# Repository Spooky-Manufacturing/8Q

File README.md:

# 8Q
<!-- ALL-CONTRIBUTORS-BADGE:START - Do not remove or modify this section -->

<!-- ALL-CONTRIBUTORS-BADGE:END -->

Computer with built-in General Purpose 8 Qubit Optical Quantum Processor

# Contributors
[Thank you to all the contributors who make this possible](./CONTRIBUTORS.md)

# Status: Moving Towards PCB!

We're beginning to layout the components and finalize the design of our quantum computer! As we continue to design the PCB, we are also working with optical engineers to make our logic gates more compact which will enable us to shrink the design even further than we already have!

### Development Board

To speed up R&D, we've decided to replace the ARM CPU with a QSeven2.0 spec'd "computer on module". There are a variety of benefits to doing this, one major benefit being that we can switch between a variety of x86 and ARM processors.

The current design effort utilizes the Congatech A50 CoM.

### Quantum Processing Unit

### QController

The QController acts as a bridge between the main (digital) computer and the quantum processor. It is responsible for storing/executing instructions, and for transferring data to/from the host and QPU.

## Features

* Quad-Core Cortex-A53
* Mali-T720 MP2 GPU
* 1x DDR4 Ram Slot (Max 64GB)
* 32/64 Bit Compatible
* Linux Capable

## Files

#### Hardware Design Files

| Type                | Directory   | Filename         | Description                |
| ------------------- | ----------- | ---------------- | -------------------------- |
| Project File        | [8Q/](./8Q) | 8Q.pro           | Main KiCAD Project File    |
| PCB Design File     | [8Q/](./8Q) | 8Q.kicad_PCB     | Main KiCAD PCB File        |
| Board Schematic     | [8Q/](./8Q) | cpu.sch          | Main CPU Schematic         |
| Board Schematic     | [8Q/](./8Q) | cpu_power.sch    | CPU Power Schematic        |
| Board Schematic     | [8Q/](./8Q) | RAM.sch          | CPU RAM Schematic          |
| QCore Schematic     | [8Q/](./8Q) | qpu.sch          | Main QPU Schematic         |
| QCore Schematic     | [8Q/](./8Q) | qpower.sch       | QPU Power Schematic        |
| QCore Schematic     | [8Q/](./8Q) | preprocessor.sch | QPU Control Unit Schematic |
| Manufacturing Files | 8Q/gerber   | none             | none (gerber files)        |
| Manufacturing Files | 8Q/assembly | none             | none (assembly files)      |

#### Documentation Files

| Type              | Directory                     | Filename         | Description                                |
| ----------------- | ----------------------------- | ---------------- | ------------------------------------------ |
| Makefile          | [docs/](./docs)               | Makefile         | Used to build documentation                |
| Folder            | [docs/build/](./docs/build)   | *                | Build files for docs                       |
| Folder            | [docs/source/](./docs/source) | *                | Documentation source files                 |
| Folder            | [docs/source/imgs/](./docs/source/imgs) | *      | Image files                                |
| ReStructured Text | [docs/source/](./docs/source) | architecture.rst | Instruction Set Architecture Documentation |
| ReStructured Text | [docs/source/](./docs/source) | board.rst        | Board Hardware Information                 |
| Python            | [docs/source/](./docs/source) | conf.py          | Docs Generator Configs                     |
| ReStructured Text | [docs/source/](./docs/source) | index.rst        | Documentation Home Page                    |
| ReStructured Text | [docs/source/](./docs/source) | programming.rst  | Programming Documentation                  |

#### Firmware/Software Sources

None: [src/](./src)

#### Development Tools

None: [tools/](./tools)

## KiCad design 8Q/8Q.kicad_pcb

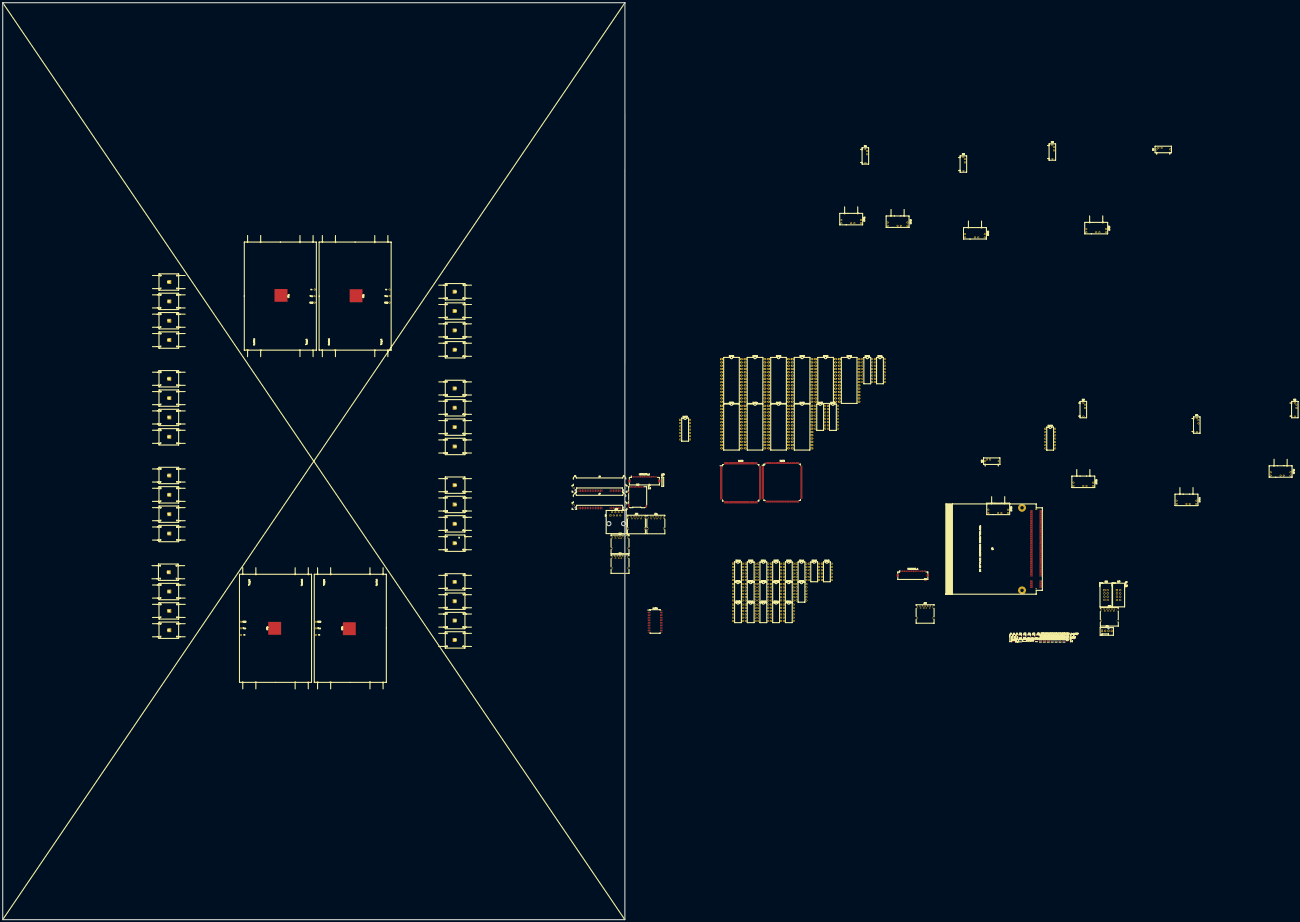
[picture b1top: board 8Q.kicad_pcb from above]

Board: 2 copper layers, 482.5 x 711.0 mm, 157 parts (0 on the bottom side), 266 nets, no tracks yet.

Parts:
C262292_1, C262292_2: LVDS Display; Hirose_FH12-40S-0.5SH_1x40-1MP_P0.50mm_Horizontal
CH1: Macro-CH-Gate; CH-Gate
CX1: Macro-CX-Gate; CX-Gate
CY1: Macro-CY-Gate; CY-Gate
CZ1: Macro-CZ-Gate; CZ-Gate
D1: GreenLED; LED_0603_1608Metric
D2: BlueLED; LED_0603_1608Metric
D5, D6, D7, D8, D9, D10, D11, D12, D13, D14, D15, D16, D17, D18, D19, D20: 1SS367,H3F; D_SOD-323
H1, H2, H3, H4, H5, H6, H7, H8: Macro-H-Gate; H-Gate
J1: TEMP; PinHeader_1x02_P1.00mm_Vertical
J2: 1 WIRE BUS; PinHeader_1x01_P1.00mm_Vertical
J3: SMBUS; PinHeader_1x03_P1.00mm_Vertical
J4: GP0_I2C; PinHeader_1x02_P1.00mm_Vertical
J5: HDA/I2C; PinHeader_1x05_P1.00mm_Vertical
J6: SATA0; SATA_Amphenol_10029364-001LF_Horizontal
J7: SATA1; SATA_Amphenol_10029364-001LF_Horizontal
J8: CAN BUS; PinHeader_1x02_P1.00mm_Vertical
J9: UART; PinHeader_1x04_P1.00mm_Vertical
J12: 8P8C_LED_Shielded; RJ45_Amphenol_54602-x08_Horizontal
J13: Watchdog; PinHeader_1x02_P1.00mm_Vertical
J15: SD_Card; microSD_HC_Hirose_DM3AT-SF-PEJM5
J19: BIOS_DISABLE; PinHeader_1x02_P1.00mm_Vertical
J20: AVR-JTAG-10; IDC-Header_2x04_P2.54mm_Vertical
J21: USB3_A; USB3_A_Molex_48393-001
J22: LDC; IDC-Header_2x04_P2.54mm_Vertical
J23: GPIO; PinHeader_1x08_P1.00mm_Vertical
J24, J25, J26, J27, J28: USB_A; USB3_A_Molex_48393-001
M1, M2, M3, M4, M5, M6, M7, M8: Macro-Measure; Measure
M9: CPU_FAN; FanPinHeader_1x04_P2.54mm_Vertical
Q1, Q2, Q3, Q4: Q_PNP_BCE; SOT-23
Q5: Q_NPN_BCE; SOT-23
Q6: Q7; MXM2.0
R1, R2, R3, R4: 10k; R_0402_1005Metric
R5, R6, R7, R8: 1k; R_0402_1005Metric
R9: 10ohm; R_0402_1005Metric
R10: 1M; R_0402_1005Metric
SPE1, SPE2, SPE3, SPE4, SPE5, SPE6, SPE7, SPE8: Macro-Photon-Source; Photon-Source
U1, U2, U180, U182, U184, U185, U186, U187: USBLC6-2P6; SOT-666
U175, U176: HEF4093B; DIP-14_W7.62mm
U178: S5933_PQ160; PQFP-160_28x28mm_P0.65mm
U179: STM32F429BITx; LQFP-208_28x28mm_P0.5mm
U181, U183, U196, U197: 74LS590; DIP-16_W7.62mm
U188, U189, U192, U193, U194, U195, U198, U199, U204, U205: 28C256; DIP-28_W15.24mm_LongPads
U208: FM1608B-SG; SOIC-28W_7.5x17.9mm_P1.27mm
U210, U211, U212, U213, U214, U215, U216, U217, U218, U219, U220, U221, U222, U223, U224, U225, U226, U227, U228: 74LS243; DIP-12_W7.62mm
X1, X2, X3, X4, X5, X6, X7, X8: Macro-X-Gate; X-Gate
Y1, Y2, Y3, Y4, Y5, Y6, Y7, Y8: Macro-Y-Gate; Y-Gate
Z1, Z2, Z3, Z4, Z5, Z6, Z7, Z8: Macro-Z-Gate; Z-Gate

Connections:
+3V3: C262292_1.2, C262292_1.3, C262292_2.2, C262292_2.3, J20.4, J20.7, Q5.2
+5V: M1.3, M2.3, M3.3, M4.3, M5.3, M6.3, M7.3, M8.3, Q6.205, Q6.206, Q6.211, Q6.212, Q6.213, Q6.214, Q6.215, Q6.216, Q6.217, Q6.218, Q6.219, Q6.220, Q6.221, Q6.222, Q6.223, Q6.224, Q6.225, Q6.226, Q6.227, Q6.228, Q6.229, Q6.230, R1.1, R2.1, R3.1, R4.1, U188.20, U188.28, U189.20, U189.28, U192.20, U192.28, U193.20, U193.28, U194.20, U194.28, U195.20, U195.28, U198.20, U198.28, U199.20, U199.28, U204.20, U204.28, U205.20, U205.28, U208.28
BIOS_DISABLE: J19.2, Q6.41
CAN0_RX: J8.2, Q6.130
CAN0_TX: J8.1, Q6.129
CCD: U210.6, U210.8
CH: U219.5, U219.9
CQ1D: U210.3, U210.11
CQ2D: U210.4, U210.10
CQ3D: U210.5, U210.9
CTD: U228.3, U228.11
CY: U219.3, U219.11
CZ: U219.4, U219.10
DP_HDMI_HPD: C262292_1.7, C262292_1.10, C262292_1.13, C262292_1.16, C262292_1.19, C262292_1.22, C262292_1.25, C262292_1.30, C262292_2.7, C262292_2.10, C262292_2.13, C262292_2.16, C262292_2.19, C262292_2.22, C262292_2.25, C262292_2.30, CH1.10, CX1.10, CY1.10, CZ1.10, D5.2, D6.2, D7.2, D8.2, D9.2, D10.2, D11.2, D12.2, D13.2, D14.2, D15.2, D16.2, D17.2, D18.2, D19.2, D20.2, J19.1, J20.2, J24.4, J24.5, J25.4, J25.5, J26.4, J26.5, J27.4, J27.5, J28.4, J28.5, M1.4, M2.4, M3.4, M4.4, M5.4, M6.4, M7.4, M8.4, M9.1, Q1.2, Q2.2, Q3.2, Q4.2, Q6.1, Q6.2, Q6.23, Q6.24, Q6.25, Q6.34, Q6.39, Q6.40, Q6.57, Q6.58, Q6.73, Q6.74, Q6.97, Q6.98, Q6.117, Q6.118, Q6.135, Q6.136, Q6.141, Q6.142, Q6.147, Q6.148, Q6.153, Q6.159, Q6.160, Q6.165, Q6.166, Q6.183, Q6.184, Q6.197, Q6.198, R9.2, R10.2, SPE1.8, SPE2.8, SPE3.8, SPE4.8, SPE5.8, SPE6.8, SPE7.8, SPE8.8, U1.2, U2.2, U180.2, U182.2, U184.2, U185.2, U186.2, U187.2, U208.14, U210.7, U211.7, U212.7, U213.7, U214.7, U215.7, U216.7, U217.7, U218.7, U219.7, U220.7, U221.7, U222.7, U223.7, U224.7, U225.7, U226.7, U227.7, U228.7
FAN_PWM: M9.4, Q6.196
FAN_TACHO: M9.3, Q6.195
GBE0+: J12.1, Q6.12
GBE0-: J12.2, Q6.10
GBE1+: J12.3, Q6.11
GBE1-: J12.6, Q6.9
GBE2+: J12.4, Q6.6
GBE2-: J12.5, Q6.4
GBE3+: J12.7, Q6.5
GBE3-: J12.8, Q6.3
GBE_10: Q6.13, R8.2
GBE_100: Q6.7, R5.2
GBE_1000: Q6.8, R6.2
GBE_ACT: Q6.14, R7.1
GNDA: SPE1.7, SPE2.7, SPE3.7, SPE4.7, SPE5.7, SPE6.7, SPE7.7, SPE8.7
GP0_I2C_CLK: J4.1, Q6.66
GP1_WIRE_BUS: J2.1, Q6.124
GPO_I2C_DAT: J4.2, Q6.68
HDA_BITCLK: J5.3, Q6.63
HDA_RST: J5.2, Q6.61
HDA_SDI: J5.4, Q6.65
HDA_SDO: J5.5, Q6.67
HDA_SYNC: J5.1, Q6.59
JTAG_TCK: J20.1, Q6.207
JTAG_TDO: J20.3, Q6.209
JTAG_TMS: J20.5, Q6.210
JTAG_TRST: J20.8, Q6.204
LPC_AD0_GPIO0: J22.3, J23.1, Q6.185
LPC_AD1_GPIO1: J22.7, J23.2, Q6.186
LPC_AD2_GPIO2: J22.4, J23.3, Q6.187
LPC_AD3_GPIO3: J22.8, J23.4, Q6.188
LPC_CLK_GPIO4: J22.1, J23.5, Q6.189
LPC_FRAME_GPIO5: J22.5, J23.6, Q6.190
LPC_LDRQ_GPIO7: J22.6, J23.8, Q6.192
LVDS_A0+: C262292_1.9, Q6.99
LVDS_A0-: C262292_1.8, Q6.101
LVDS_A1+: C262292_1.12, Q6.103
LVDS_A1-: C262292_1.11, Q6.105
LVDS_A2+: C262292_1.15, Q6.107
LVDS_A2-: C262292_1.14, Q6.109
LVDS_A3+: C262292_1.21, Q6.113
LVDS_A3-: C262292_1.20, Q6.115
LVDS_A_CLK+: C262292_1.18, Q6.119
LVDS_A_CLK-: C262292_1.17, Q6.121
LVDS_B0+: C262292_2.9, Q6.100
LVDS_B0-: C262292_2.8, Q6.102
LVDS_B1+: C262292_2.12, Q6.104
LVDS_B1-: C262292_2.11, Q6.106
LVDS_B2+: C262292_2.15, Q6.108
LVDS_B2-: C262292_2.14, Q6.110
LVDS_B3+: C262292_2.21, Q6.114
LVDS_B3-: C262292_2.20, Q6.116
LVDS_BLT_CTRL: C262292_1.27, C262292_2.27, Q6.123
LVDS_B_CLK+: C262292_2.18, Q6.120
LVDS_B_CLK-: C262292_2.17, Q6.122
LVDS_DID_CLK: C262292_1.24, C262292_2.24, Q6.127
LVDS_DID_DAT: C262292_1.23, C262292_2.23, Q6.125
LVDS_PPEN: C262292_1.26, C262292_2.26, Q6.111
unnamed: D1.1, Q1.3
unnamed: D1.2, R1.2
unnamed: D2.1, Q4.3
unnamed: D2.2, R2.2
unnamed: J15.3, J15.6
unnamed: J21.2, U1.6
unnamed: J21.3, U1.1
unnamed: J21.5, U2.6
unnamed: J21.6, U2.1
unnamed: J21.8, U180.6
unnamed: J21.4, J21.7, J21.9, J21.10, U180.1
unnamed: J24.2, U182.1
unnamed: J24.3, U182.6
unnamed: J25.2, U184.1
unnamed: J25.3, U184.6
unnamed: J26.2, U185.1
unnamed: J26.3, U185.6
unnamed: J27.2, U186.1
unnamed: J27.3, U186.6
unnamed: J28.2, U187.1
unnamed: J28.3, U187.6
unnamed: M1.2, U175.1
unnamed: M2.1, U176.12
unnamed: M3.2, U175.5
unnamed: M4.1, U175.8
unnamed: M5.2, U176.8
unnamed: M6.1, U176.5
unnamed: M7.2, U175.12
unnamed: M8.1, U176.1
unnamed: Q1.1, R5.1
unnamed: Q2.1, R7.2
unnamed: Q3.1, R8.1
unnamed: Q4.1, R6.1
unnamed: X1.2, Y1.2, Z1.2
unnamed: X1.1, Y1.1, Z1.1
unnamed: X2.1, Y2.1, Z2.1
unnamed: X2.2, Y2.2, Z2.2
unnamed: X3.2, Y3.2, Z3.2
unnamed: X3.1, Y3.1, Z3.1
unnamed: X4.1, Y4.1, Z4.1
unnamed: X4.2, Y4.2, Z4.2
unnamed: X5.2, Y5.2, Z5.2
unnamed: X5.1, Y5.1, Z5.1
unnamed: X6.1, Y6.1, Z6.1
unnamed: X6.2, Y6.2, Z6.2
unnamed: X7.2, Y7.2, Z7.2
unnamed: X7.1, Y7.1, Z7.1
unnamed: X8.1, Y8.1, Z8.1
unnamed: X8.2, Y8.2, Z8.2
unnamed: U181.8, U183.8
unnamed: U181.9, U183.12
unnamed: U181.16, U183.16
unnamed: U188.14, U193.14, U194.14, U198.14, U204.14
unnamed: U189.14, U192.14, U195.14, U199.14, U205.14
unnamed: U196.8, U197.8
unnamed: U196.9, U197.12
unnamed: U196.16, U197.16
unnamed: U210.1, U211.1, U212.1, U213.1, U214.1, U215.1, U216.1, U217.1, U218.1, U219.1, U220.1, U221.1, U222.1, U223.1, U224.1, U225.1, U226.1, U227.1, U228.1
Q1-Out: M8.2, U176.2
Q1C: U213.5, U213.9
Q1D: U211.6, U211.8
Q1M: U213.4, U213.10
Q1SR: SPE1.2, U212.3, U212.11
Q1T: SPE1.1, U212.4, U212.10
Q1X: U212.5, U212.9
Q1Y: U212.6, U212.8
Q1Z: U213.3, U213.11
Q2-Out: M6.2, U176.6
Q2C: U215.4, U215.10
Q2D: U211.5, U211.9
Q2M: U215.3, U215.11
Q2SR: SPE3.2, U213.6, U213.8
Q2T: SPE3.1, U214.3, U214.11
Q2X: U214.4, U214.10
Q2Y: U214.5, U214.9
Q2Z: U214.6, U214.8
Q3-Out: M4.2, U175.9
Q3C: U217.3, U217.11
Q3D: U211.4, U211.10
Q3M: U216.6, U216.8
Q3SR: SPE5.2, U215.5, U215.9
Q3T: SPE5.1, U215.6, U215.8
Q3X: U216.3, U216.11
Q3Y: U216.4, U216.10
Q3Z: U216.5, U216.9
Q4-Out: M2.2, U176.13
Q4C: U218.6, U218.8
Q4D: U211.3, U211.11
Q4M: U218.5, U218.9
Q4SR: SPE7.2, U217.4, U217.10
Q4T: SPE7.1, U217.5, U217.9
Q4X: U217.6, U217.8
Q4Y: U218.3, U218.11
Q4Z: U218.4, U218.10
Q5-Out: M1.1, U175.2
Q5C: U221.5, U221.9
Q5D: U227.3, U227.11
Q5M: U221.4, U221.10
Q5SR: SPE8.2, U220.3, U220.11
Q5T: SPE8.1, U220.4, U220.10
Q5X: U220.5, U220.9
Q5Y: U220.6, U220.8
Q5Z: U221.3, U221.11
Q6-Out: M3.1, U175.6
Q6C: U223.4, U223.10
Q6D: U227.4, U227.10
Q6M: U223.3, U223.11
Q6SR: SPE6.2, U221.6, U221.8
Q6T: SPE6.1, U222.3, U222.11
Q6X: U222.4, U222.10
Q6Y: U222.5, U222.9
Q6Z: U222.6, U222.8
Q7-Out: M5.1, U176.9
Q7C: U225.3, U225.11
Q7D: U227.5, U227.9
Q7M: U224.6, U224.8
Q7SR: SPE4.2, U223.5, U223.9
Q7T: SPE4.1, U223.6, U223.8
Q7X: U224.3, U224.11
Q7Y: U224.4, U224.10
Q7Z: U224.5, U224.9
Q8-Out: M7.1, U175.13
Q8C: U226.6, U226.8
Q8D: U227.6, U227.8
Q8M: U226.5, U226.9
Q8SR: SPE2.2, U225.4, U225.10
Q8T: SPE2.1, U225.5, U225.9
Q8X: U225.6, U225.8
Q8Y: U226.3, U226.11
Q8Z: U226.4, U226.10
QA0: U181.15, U188.10, U189.10, U192.10, U193.10, U194.10, U195.10, U198.10, U199.10, U204.10, U205.10
QA1: U181.1, U188.9, U189.9, U192.9, U193.9, U194.9, U195.9, U198.9, U199.9, U204.9, U205.9
QA2: U181.2, U188.8, U189.8, U192.8, U193.8, U194.8, U195.8, U198.8, U199.8, U204.8, U205.8
QA3: U181.3, U188.7, U189.7, U192.7, U193.7, U194.7, U195.7, U198.7, U199.7, U204.7, U205.7
QA4: U181.4, U188.6, U189.6, U192.6, U193.6, U194.6, U195.6, U198.6, U199.6, U204.6, U205.6
QA5: U181.5, U188.5, U189.5, U192.5, U193.5, U194.5, U195.5, U198.5, U199.5, U204.5, U205.5
QA6: U181.6, U188.4, U189.4, U192.4, U193.4, U194.4, U195.4, U198.4, U199.4, U204.4, U205.4
QA7: U181.7, U188.3, U189.3, U192.3, U193.3, U194.3, U195.3, U198.3, U199.3, U204.3, U205.3
QA8: U183.15, U188.25, U189.25, U192.25, U193.25, U194.25, U195.25, U198.25, U199.25, U204.25, U205.25
QA9: U183.1, U188.24, U189.24, U192.24, U193.24, U194.24, U195.24, U198.24, U199.24, U204.24, U205.24
QA10: U183.2, U188.21, U189.21, U192.21, U193.21, U194.21, U195.21, U198.21, U199.21, U204.21, U205.21
QA11: U183.3, U188.23, U189.23, U192.23, U193.23, U194.23, U195.23, U198.23, U199.23, U204.23, U205.23
QA12: U183.4, U188.2, U189.2, U192.2, U193.2, U194.2, U195.2, U198.2, U199.2, U204.2, U205.2
QA13: U183.5, U188.26, U189.26, U192.26, U193.26, U194.26, U195.26, U198.26, U199.26, U204.26, U205.26
QA14: U183.6, U188.1, U189.1, U192.1, U193.1, U194.1, U195.1, U198.1, U199.1, U204.1, U205.1
Q_OE: U188.22, U189.22, U192.22, U193.22, U194.22, U195.22, U198.22, U199.22, U204.22, U205.22
Q_WE: U188.27, U189.27, U192.27, U193.27, U194.27, U195.27, U198.27, U199.27, U204.27, U205.27
RSTBTN: J20.6, Q6.28
SDIO_CD: J15.10, Q6.43
SDIO_CLK: J15.5, Q6.42
SDIO_CMD: J15.2, Q6.45
SDIO_DAT0: J15.7, Q6.49
SDIO_DAT1: J15.8, Q6.48
SDIO_DAT2: J15.9, Q6.51
SDIO_DAT3: J15.1, Q6.50
SDIO_PWR: J15.4, Q5.1, Q5.3, Q6.47
SDIO_WP: J15.11, Q6.46
SERIRQ_GPIO6: J22.2, J23.7, Q6.191
SMCLK: J3.3, Q6.60
SMDAT: J3.2, Q6.62
SM_ALERT: J3.1, Q6.64
SWAP: U219.6, U219.8
ScreenLEDAnode: C262292_1.39, C262292_1.40, C262292_2.39, C262292_2.40
ScreenLEDCathode: C262292_1.31, C262292_1.32, C262292_2.31, C262292_2.32
THRM: J1.1, Q6.69
THRMTRIP: J1.2, Q6.71
TQ5: U228.4, U228.10
TQ6: U228.5, U228.9
TQ7: U228.6, U228.8
UART0_CTS: J9.1, Q6.178
UART0_RTS: J9.2, Q6.172
UART0_RX: J9.3, Q6.177
UART0_TX: J9.4, Q6.171
USB_ID: Q6.92, R9.1
USB_P0+: D11.1, Q6.96, U182.4
USB_P0-: D12.1, Q6.94, U182.3
USB_P1+: D13.1, Q6.95, U184.4
USB_P1-: D14.1, Q6.93, U184.3
USB_P2+: D15.1, Q6.90, U185.4
USB_P2-: D16.1, Q6.88, U185.3
USB_P3+: D17.1, Q6.89, U186.4
USB_P3-: D18.1, Q6.87, U186.3
USB_P4+: D19.1, Q6.84, U187.4
USB_P4-: D20.1, Q6.82, U187.3
USB_P5+: D5.1, Q6.83, U1.3
USB_P5-: D8.1, Q6.81, U1.4
USB_RX0+: D6.1, Q6.78, U2.3
USB_RX0-: D9.1, Q6.76, U2.4
USB_TX0+: D7.1, Q6.77, U180.3
USB_TX0-: D10.1, Q6.75, U180.4
USB_VBUS: J21.1, J24.1, J25.1, J26.1, J27.1, J28.1, Q6.91, R10.1, U1.5, U2.5, U180.5, U182.5, U184.5, U185.5, U186.5, U187.5
VSS: CH1.9, CX1.9, CY1.9, CZ1.9
WDOUT: J13.2, Q6.72
WDTRIG: J13.1, Q6.70

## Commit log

2020-07-02 new file: 8Q/8Q-cache.lib new file: 8Q/8Q.kicad_pcb new file: 8Q/8Q.pro new file: 8Q/8Q.sch new file: 8Q/cpu.sch new file: 8Q/cpu_power.sch new file: 8Q/power.sch new file: 8Q/preprocessor.sch new fi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
2020-07-02 modified: README.md
2020-07-02 new file: 8Q/8_qp_io.sch Added Quantum Processor I/O page to schematics
2020-07-03 modified: 8Q/8Q-cache.lib modified: 8Q/8Q.sch modified: 8Q/8_qp_io.sch new file: 8Q/RAM.sch deleted: 8Q/_saved_RAM.sch modified: 8Q/cpu.sch modified: 8Q/cpu_power.sch modified: 8Q/power.sch modified: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
2020-07-06 Update issue templates
2020-07-06 modified: .gitignore modified: README.md
2020-07-06 docs: update README.md [skip ci]
2020-07-06 docs: create .all-contributorsrc [skip ci]
2020-07-06 modified: .all-contributorsrc new file: CONTRIBUTORS.md
2020-07-06 docs: update .all-contributorsrc [skip ci]
2020-07-06 modified: .all-contributorsrc modified: CONTRIBUTORS.md modified: README.md Testing all-contributors setup (they really should let you do this on another branch...)
2020-07-06 modified: CONTRIBUTORS.md more testing...
2020-07-06 modified: .all-contributorsrc modified: CONTRIBUTORS.md
2020-07-06 fixed JSON error: unexpected token '
2020-07-06 modified: .all-contributorsrc
2020-07-06 modified: CONTRIBUTORS.md modified: README.md
2020-07-06 Update .all-contributorsrc
2020-07-06 modified: CONTRIBUTORS.md
2020-07-06 docs: add NoahGWood as a contributor (#5)
    * docs: update README.md [skip ci]
    * docs: update .all-contributorsrc [skip ci]
    * docs: update README.md [skip ci]
    * docs: update .all-contributorsrc [skip ci]
2020-07-06 docs: update CONTRIBUTORS.md [skip ci]
2020-07-06 docs: add NoahGWood as a contributor (#6)
    * docs: update CONTRIBUTORS.md [skip ci]
    * docs: update .all-contributorsrc [skip ci]
2020-07-06 docs: add NoahGWood as a contributor (#8)
    * docs: update CONTRIBUTORS.md [skip ci]
    * docs: update .all-contributorsrc [skip ci]
2020-07-06 new file: QCore.md new file: docs/source/imgs/cx_gate.png new file: docs/source/imgs/faint_laser.png
2020-07-06 modified: QCore.md new file: roadmap.md
2020-07-06 Added nsgate schematic Added roadmap.md modified QCore.md
2020-07-06 modified: roadmap.md Added table of contents
2020-07-06 modified: roadmap.md
2020-07-06 Fixed link to 'participating' header in roadmap
2020-07-07 new file: CONTRIBUTING.md
2020-07-07 modified: CONTRIBUTING.md
2020-07-07 new file: question.md
2020-07-07 Added DOI tag for V 0.0.0T
2020-09-19 modified: 8Q/8Q-cache.lib modified: 8Q/8Q.sch modified: 8Q/8_qp_io.sch modified: 8Q/RAM.sch new file: 8Q/control_logic.sch modified: 8Q/cpu.sch modified: 8Q/cpu_power.sch new file: 8Q/inorder.sch new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
2020-09-19 deleted: docs/source/imgs/Screenshot from 2020-07-07 18-04-51.png Accidentally added? whoops!
2021-07-13 modified: 8Q/8Q-cache.lib new file: 8Q/8Q-rescue.dcm new file: 8Q/8Q-rescue.lib modified: 8Q/8Q.kicad_pcb modified: 8Q/8Q.sch modified: 8Q/8_qp_io.sch new file: 8Q/QGates.pretty/CH-Gate.kicad_mod new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
2021-07-13 new file: 8Q/cpu-cache.lib modified: 8Q/cpu.sch new file: docs/source/imgs/cpu.png modified: roadmap.md
2022-01-26 Added description to gates.
2022-01-28 Tidy up docs
2022-01-28 Ensure vscode does not leak into repo
2022-01-28 Add generated build
2022-01-28 Fixed spelling issue
2022-02-01 fix URL to QEDA project closes #20
2022-02-14 Starting Error and quantification of Quantum Power
    1. Error
    2. Quantum Volume
    3. Circuit Level Operations/Sec?
2022-02-15 Started work on error and benchmark work.
2022-02-15 use consistent 'qubit' term
2022-02-15 clickable links for exploring content
2022-02-15 missed one
2022-03-11 Update Benchmarks.md
    Added theoretical CLOPS
2022-03-11 Created Error Calcs programs
    Error calculations started. Need to implement most.
2022-04-12 Added function for Gate error. fixed a spelling in the Error_Theory.md
2022-04-13 Added comments. I think it's clear what I'm doing but I'm doing C++ habits so it may be a bit unclear.
2022-04-13 Oops, missed one.
2022-04-13 Benchmarking functions started.
2022-05-02 Filled out outline for QV() Updated comment on IBM's most powerful computer in QV
